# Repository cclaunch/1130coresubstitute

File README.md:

1130 Core Substitute

This project is intended for IBM 1130 systems where a core memory compartment is nonfunctional and unlikely to be restored to reliable operation. The printed circuit board is inserted at the top of the core compartment and is connected via the top cables T1, T3 and T4 that are normally plugged into the SLT board for the compartment. 

It is based around a Magnetoresistive Random Access Memory (MRAM) which provides the same non-volatility as core memory even after two decades sitting without power. MRAM has infinite read and write cycles, unlike flash memory, thus it is very suitable for use in a computer.

One would disconnect the four voltage rails to the core memory compartment (+6, +3, -3 and +12) so that the compartment itself is inert. The new PCB fits in the space at the top of the compartment where the top cables were connected. It requires only three wires to connect it to the +12V and ground rails of the 1130 system. 

This first version was developed for a particular 1130 system I restored, one with 8K of 3.6 microsecond core. This fits in the B gate in compartment C1. The SLT board has a core memory stack mounted in the center and SLT cards arrayed around the outside of the stack to provide the logic to make the core work. 

The same board can be enhanced to connect to cable T2, for machines with more than 8K of memory (or any 2.2 microsecond core memory model). Assuming the machine is configured for larger memory sizes so that the proper address lines are implemented in the device controllers and central processor, this single board could implement up to the maximum 32K word memory capacity. I will outline how the enhancement might be accomplished in a document in this repository.

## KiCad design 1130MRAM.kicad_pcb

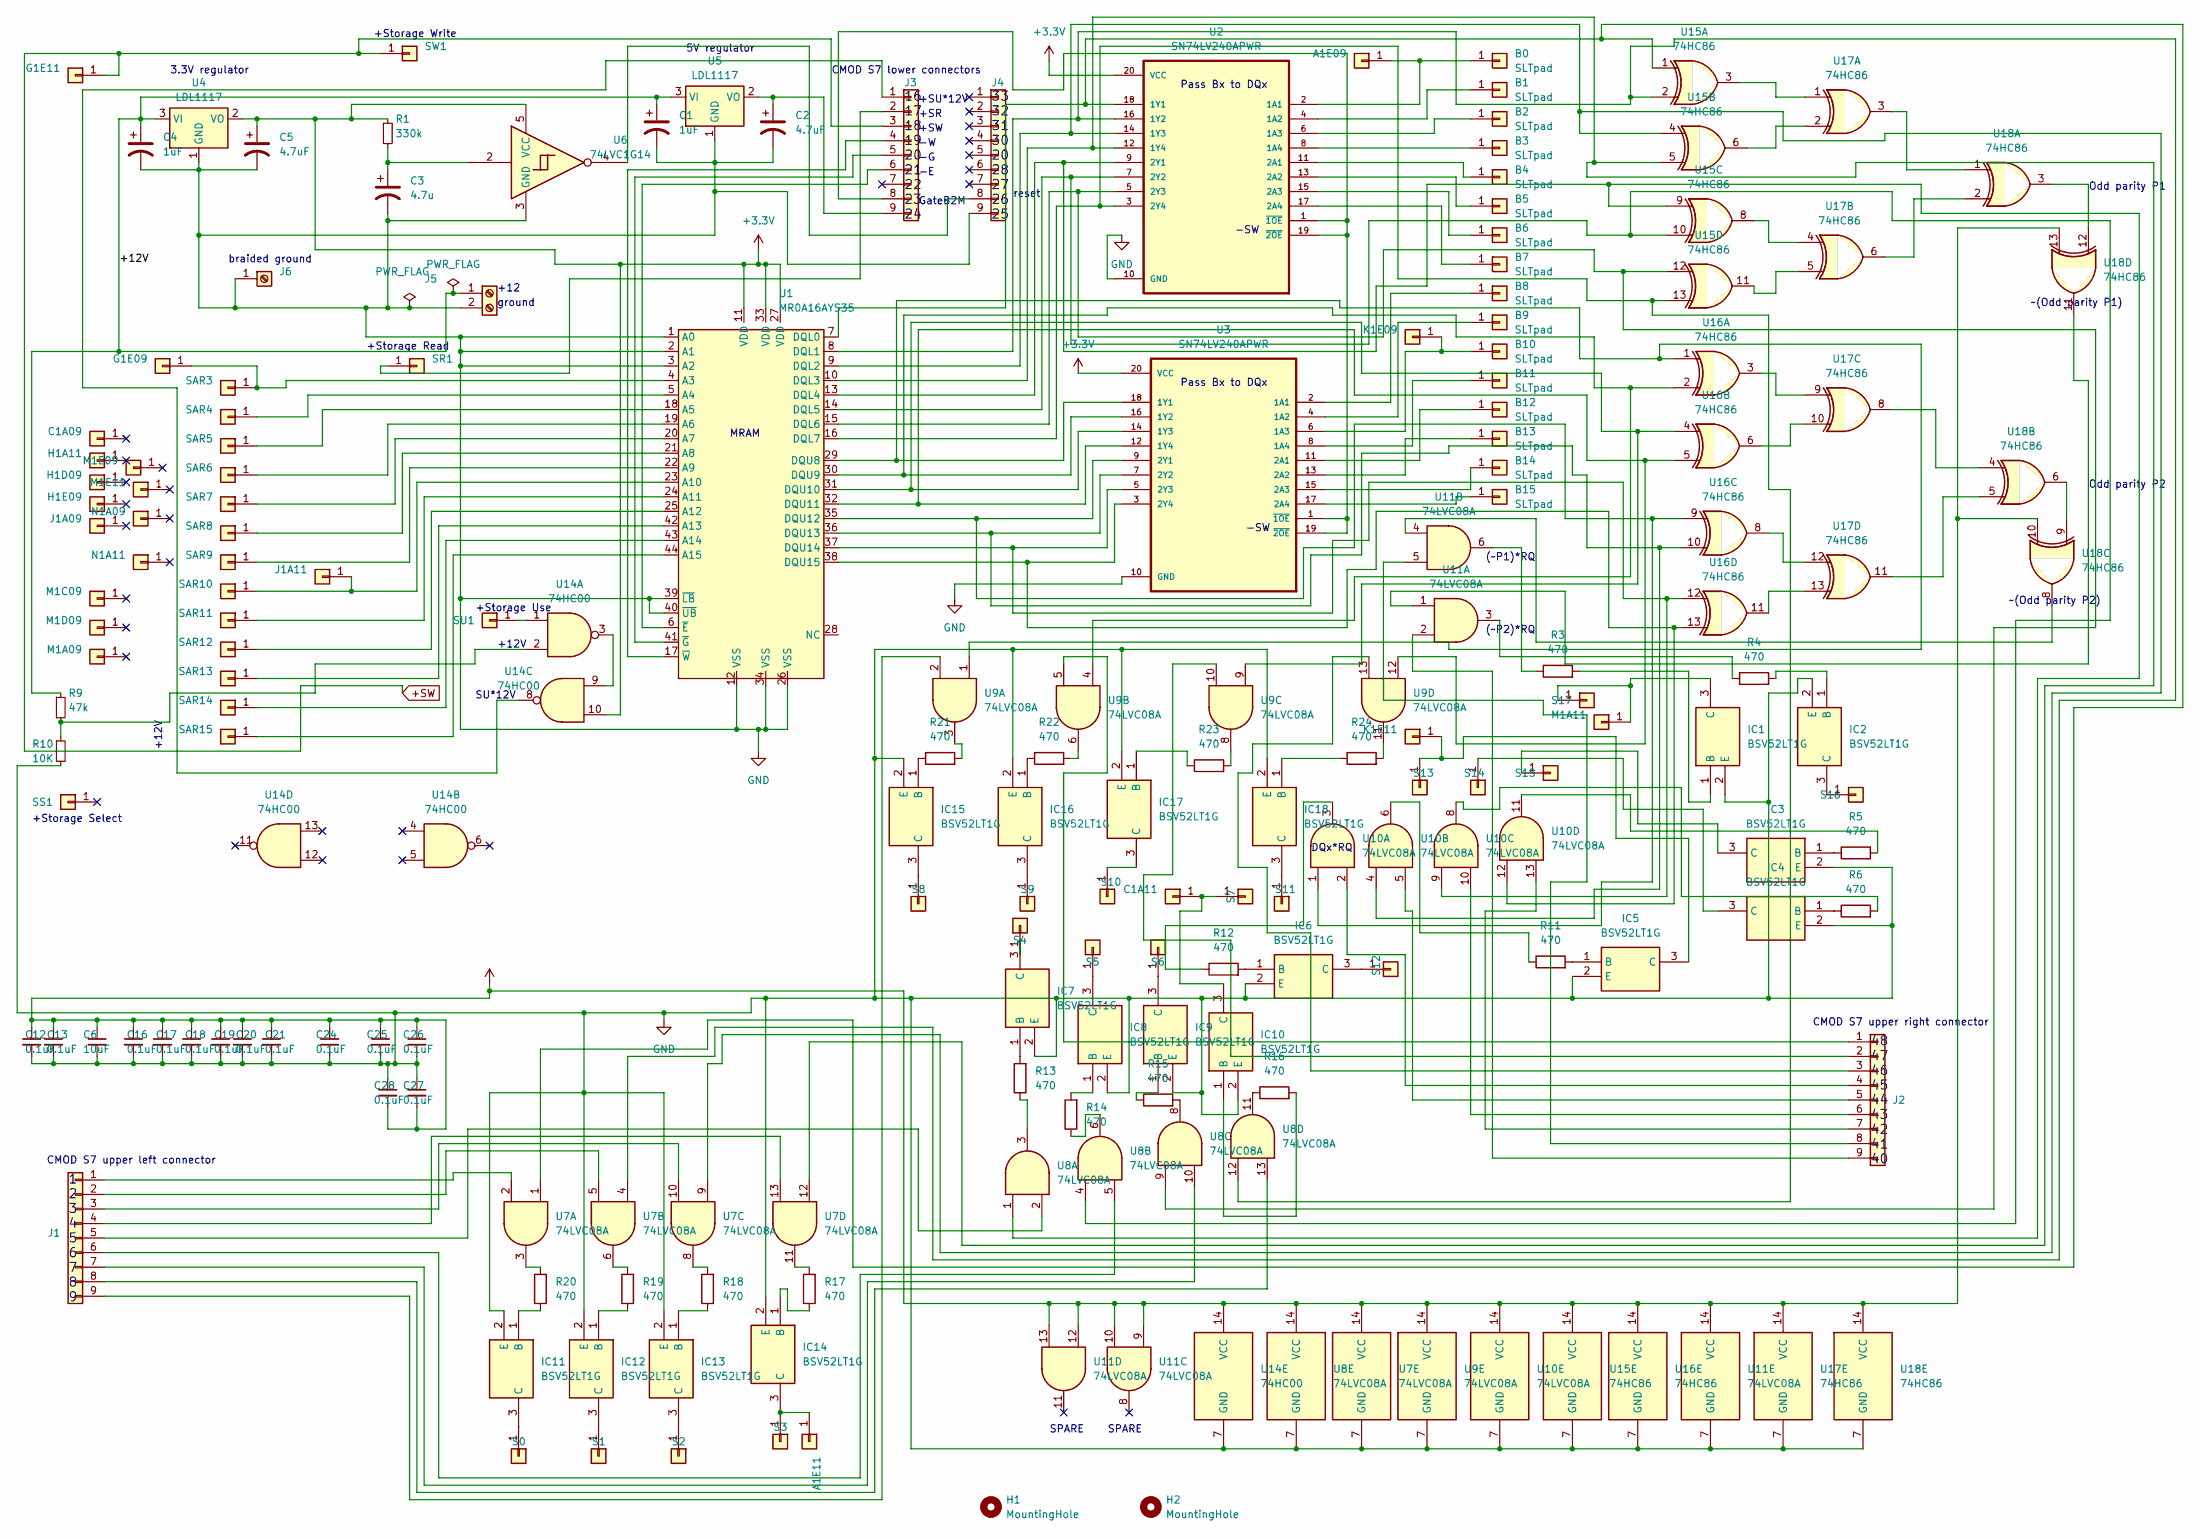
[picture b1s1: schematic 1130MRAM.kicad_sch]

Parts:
A1E09, A1E11: SLTpad; SLT
B0, B1, B2, B3, B4, B5, B6, B7, B8, B9, B10, B11, B12, B13, B14, B15: SLTpad; SLT
C1, C4: 1uF; C_0805_2012Metric
C1A09, C1A11: SLTpad; SLT
C2, C5: 4.7uF; C_0805_2012Metric
C3: 4.7u; C_0805_2012Metric
C6: 10uF; C_0805_2012Metric
C12, C13, C16, C17, C18, C19, C20, C21, C24, C25, C26, C27, C28: 0.1uF; C_0603_1608Metric
G1E09, G1E11: SLTpad; SLT
H1, H2: MountingHole; MountingHole_4.3mm_M4
H1A11, H1D09, H1E09: SLTpad; SLT
IC1, IC2, IC3, IC4, IC5, IC6, IC7, IC8, IC9, IC10, IC11, IC12, IC13, IC14, IC15, IC16, IC17, IC18: BSV52LT1G; SOT-23; Manufacturer_Part_Number BSV52LT1G; Mouser Part Number 863-BSV52LT1G
J1, J2, J3, J4: Conn_01x09_MountingPin; PinSocket_1x09_P2.54mm_Vertical
J1A09, J1A11: SLTpad; SLT
J5: Screw_Terminal_01x03; TerminalBlock_WAGO_236-102_1x02_P5.00mm_45Degree
J6: Screw_Terminal_01x01; TerminalBlock_WAGO_236-101_1x01_P5.00mm_45Degree
K1E09, K1E11: SLTpad; SLT
M1A09, M1A11, M1C09, M1D09, M1E09, M1E11: SLTpad; SLT
N1A09, N1A11: SLTpad; SLT
R1: 330k; R_0805_2012Metric
R3, R4, R5, R6, R11, R12, R13, R14, R15, R16, R17, R18, R19, R20, R21, R22, R23, R24: 470; R_0805_2012Metric
R9: 47k; R_0805_2012Metric
R10: 10K; R_0805_2012Metric
S0, S1, S2, S3, S4, S5, S6, S7, S8, S9, S10, S11, S12, S13, S14, S15, S16, S17: SLTpad; SLT
SAR3, SAR4, SAR5, SAR6, SAR7, SAR8, SAR9, SAR10, SAR11, SAR12, SAR13, SAR14, SAR15: SLTpad; SLT
SR1: SLTpad; SLT
SS1: SLTpad; SLT
SU1: SLTpad; SLT
SW1: SLTpad; SLT
U1: MR0A16AYS35; MR0A16A
U2, U3: SN74LV240APWR; sn74lvc244a
U4, U5: LDL1117; SOT-223-3_TabPin2
U6: 74LVC1G14; SOT-23-5_HandSoldering
U7, U8, U9, U10, U11: 74LVC08A; TSSOP-14_4.4x5mm_P0.65mm
U14: 74HC00; SOIC-14_3.9x8.7mm_P1.27mm
U15, U16, U17, U18: 74HC86; TSSOP-14_4.4x5mm_P0.65mm

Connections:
+3.3V: C5.1, C6.1, C12.1, C13.1, C16.1, C17.1, C18.1, C19.1, C20.1, C21.1, C24.1, C25.1, C26.1, C27.2, C28.2, R1.1, U1.11 (VDD), U1.27 (VDD), U1.33 (VDD), U2.20 (VCC), U3.20 (VCC), U4.2 (VO), U6.5 (VCC), U7.14 (VCC), U8.14 (VCC), U9.14 (VCC), U10.14 (VCC), U11.9, U11.10, U11.12, U11.13, U11.14 (VCC), U14.10, U14.14 (VCC), U15.14 (VCC), U16.14 (VCC), U17.14 (VCC), U18.10, U18.13, U18.14 (VCC)
+SW: G1E11.1, J3.3, SW1.1
/+12V: C1.1, C4.1, J5.1, R9.1, U4.3 (VI), U5.3 (VI)
GND: C1.2, C2.2, C3.2, C4.2, C5.2, C6.2, C12.2, C13.2, C16.2, C17.2, C18.2, C19.2, C20.2, C21.2, C24.2, C25.2, C26.2, C27.1, C28.1, IC1.2 (E), IC2.2 (E), IC3.2 (E), IC4.2 (E), IC5.2 (E), IC6.2 (E), IC7.2 (E), IC8.2 (E), IC9.2 (E), IC10.2 (E), IC11.2 (E), IC12.2 (E), IC13.2 (E), IC14.2 (E), IC15.2 (E), IC16.2 (E), IC17.2 (E), IC18.2 (E), J4.9, J5.2, J6.1, R10.2, U1.1 (A0), U1.2 (A1), U1.3 (A2), U1.12 (VSS), U1.26 (VSS), U1.34 (VSS), U1.39 (~LB), U1.40 (~UB), U2.10 (GND), U3.10 (GND), U4.1 (GND), U5.1 (GND), U6.3 (GND), U7.7 (GND), U8.7 (GND), U9.7 (GND), U10.7 (GND), U11.7 (GND), U14.7 (GND), U15.7 (GND), U16.7 (GND), U17.7 (GND), U18.7 (GND)
unnamed: A1E09.1, B0.1, U2.2 (1A1)
unnamed: A1E11.1, IC14.3 (C), S3.1
unnamed: B1.1, U2.4 (1A2)
unnamed: B2.1, U2.6 (1A3)
unnamed: B3.1, U2.8 (1A4)
unnamed: B4.1, U2.11 (2A1)
unnamed: B5.1, U2.13 (2A2)
unnamed: B6.1, U2.15 (2A3)
unnamed: B7.1, U2.17 (2A4)
unnamed: B8.1, U3.2 (1A1)
unnamed: B9.1, U3.4 (1A2)
unnamed: B10.1, K1E09.1, U3.6 (1A3)
unnamed: B11.1, U3.8 (1A4)
unnamed: B12.1, U3.11 (2A1)
unnamed: B13.1, U3.13 (2A2)
unnamed: B14.1, U3.15 (2A3)
unnamed: B15.1, U3.17 (2A4)
unnamed: C1A11.1, IC10.3 (C), S7.1
unnamed: C3.1, R1.2, U6.2
unnamed: G1E09.1, SAR3.1, U1.4 (A3)
unnamed: IC1.1 (B), R3.2
unnamed: IC1.3 (C), M1A11.1, S17.1
unnamed: IC2.1 (B), R4.2
unnamed: IC2.3 (C), S16.1
unnamed: IC3.1 (B), R5.1
unnamed: IC3.3 (C), S15.1
unnamed: IC4.1 (B), R6.1
unnamed: IC4.3 (C), S14.1
unnamed: IC5.1 (B), R11.2
unnamed: IC5.3 (C), K1E11.1, S13.1
unnamed: IC6.1 (B), R12.2
unnamed: IC6.3 (C), S12.1
unnamed: IC7.1 (B), R13.2
unnamed: IC7.3 (C), S4.1
unnamed: IC8.1 (B), R14.2
unnamed: IC8.3 (C), S5.1
unnamed: IC9.1 (B), R15.1
unnamed: IC9.3 (C), S6.1
unnamed: IC10.1 (B), R16.2
unnamed: IC11.1 (B), R20.1
unnamed: IC11.3 (C), S0.1
unnamed: IC12.1 (B), R19.1
unnamed: IC12.3 (C), S1.1
unnamed: IC13.1 (B), R18.1
unnamed: IC13.3 (C), S2.1
unnamed: IC14.1 (B), R17.1
unnamed: IC15.1 (B), R21.1
unnamed: IC15.3 (C), S8.1
unnamed: IC16.1 (B), R22.1
unnamed: IC16.3 (C), S9.1
unnamed: IC17.1 (B), R23.1
unnamed: IC17.3 (C), S10.1
unnamed: IC18.1 (B), R24.1
unnamed: IC18.3 (C), S11.1
unnamed: J1.1, U7.2
unnamed: J1.2, U7.5
unnamed: J1.3, U7.10
unnamed: J1.4, U7.13
unnamed: J1.5, U8.2
unnamed: J1.6, U8.5
unnamed: J1.7, U8.10
unnamed: J1.8, U8.13
unnamed: J1.9, U9.2
unnamed: J1A11.1, SAR10.1, U1.23 (A10)
unnamed: J2.1, U9.5
unnamed: J2.2, U9.10
unnamed: J2.3, U9.13
unnamed: J2.4, U10.2
unnamed: J2.5, U10.5
unnamed: J2.6, U10.10
unnamed: J2.7, U10.13
unnamed: J2.8, U11.5
unnamed: J2.9, U11.2
unnamed: J3.1, U14.8
unnamed: J3.2, SR1.1
unnamed: J3.4, U1.17 (~W)
unnamed: J3.5, U1.41 (~G)
unnamed: J3.6, U1.6 (~E)
unnamed: J3.8, U2.1 (~1OE), U2.19 (~2OE), U3.1 (~1OE), U3.19 (~2OE)
unnamed: C2.1, J3.9, U5.2 (VO)
unnamed: J4.8, U6.4
unnamed: R3.1, U11.6
unnamed: R4.1, U11.3
unnamed: R5.2, U10.11
unnamed: R6.2, U10.8
unnamed: R9.2, R10.1, U14.2
unnamed: R11.1, U10.6
unnamed: R12.1, U10.3
unnamed: R13.1, U8.3
unnamed: R14.1, U8.6
unnamed: R15.2, U8.8
unnamed: R16.1, U8.11
unnamed: R17.2, U7.11
unnamed: R18.2, U7.8
unnamed: R19.2, U7.6
unnamed: R20.2, U7.3
unnamed: R21.2, U9.3
unnamed: R22.2, U9.6
unnamed: R23.2, U9.8
unnamed: R24.2, U9.11
unnamed: SAR4.1, U1.5 (A4)
unnamed: SAR5.1, U1.18 (A5)
unnamed: SAR6.1, U1.19 (A6)
unnamed: SAR7.1, U1.20 (A7)
unnamed: SAR8.1, U1.21 (A8)
unnamed: SAR9.1, U1.22 (A9)
unnamed: SAR11.1, U1.24 (A11)
unnamed: SAR12.1, U1.25 (A12)
unnamed: SAR13.1, U1.42 (A13)
unnamed: SAR14.1, U1.43 (A14)
unnamed: SAR15.1, U1.44 (A15)
unnamed: SU1.1, U14.1
unnamed: U1.7 (DQL0), U2.18 (1Y1), U7.1, U15.1
unnamed: U1.8 (DQL1), U2.16 (1Y2), U7.4, U15.2
unnamed: U1.9 (DQL2), U2.14 (1Y3), U7.9, U15.4
unnamed: U1.10 (DQL3), U2.12 (1Y4), U7.12, U15.5
unnamed: U1.13 (DQL4), U2.9 (2Y1), U8.1, U15.9
unnamed: U1.14 (DQL5), U2.7 (2Y2), U8.4, U15.10
unnamed: U1.15 (DQL6), U2.5 (2Y3), U8.9, U15.12
unnamed: U1.16 (DQL7), U2.3 (2Y4), U8.12, U15.13
unnamed: U1.29 (DQU8), U3.18 (1Y1), U9.1, U16.1
unnamed: U1.30 (DQU9), U3.16 (1Y2), U9.4, U16.2
unnamed: U1.31 (DQU10), U3.14 (1Y3), U9.9, U16.4
unnamed: U1.32 (DQU11), U3.12 (1Y4), U9.12, U16.5
unnamed: U1.35 (DQU12), U3.9 (2Y1), U10.1, U16.9
unnamed: U1.36 (DQU13), U3.7 (2Y2), U10.4, U16.10
unnamed: U1.37 (DQU14), U3.5 (2Y3), U10.9, U16.12
unnamed: U1.38 (DQU15), U3.3 (2Y4), U10.12, U16.13
unnamed: U11.1, U18.11
unnamed: U11.4, U18.8
unnamed: U14.3, U14.9
unnamed: U15.3, U17.1
unnamed: U15.6, U17.2
unnamed: U15.8, U17.4
unnamed: U15.11, U17.5
unnamed: U16.3, U17.9
unnamed: U16.6, U17.10
unnamed: U16.8, U17.12
unnamed: U16.11, U17.13
unnamed: U17.3, U18.1
unnamed: U17.6, U18.2
unnamed: U17.8, U18.4
unnamed: U17.11, U18.5
unnamed: U18.6, U18.9
unnamed: U18.3, U18.12

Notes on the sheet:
+12V
+SW
3.3V regulator
+Storage Read
Pass Bx to DQx
CMOD S7 upper right connector
1 2 3 4 5 6 7 8 9
-SW
+Storage Write
Odd parity P2
(~P2)*RQ
GateB2M
SPARE
braided ground
CMOD S7 upper left connector
33 32 31 30 20 28 27 26 25
+12
reset
MRAM
+SR
(~P1)*RQ
ground
~(Odd parity P1)
48 47 46 45 44 43 42 41 40
DQx*RQ
+Storage Select
SU*12V
+Storage Use
+SU*12V
16 17 18 19 20 21 22 23 24
5V regulator
Odd parity P1
~(Odd parity P2)
CMOD S7 lower connectors

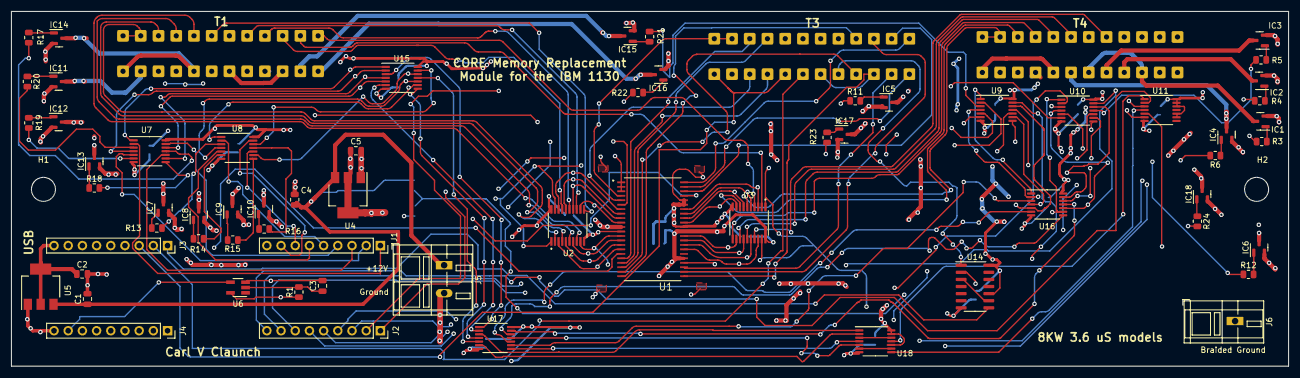
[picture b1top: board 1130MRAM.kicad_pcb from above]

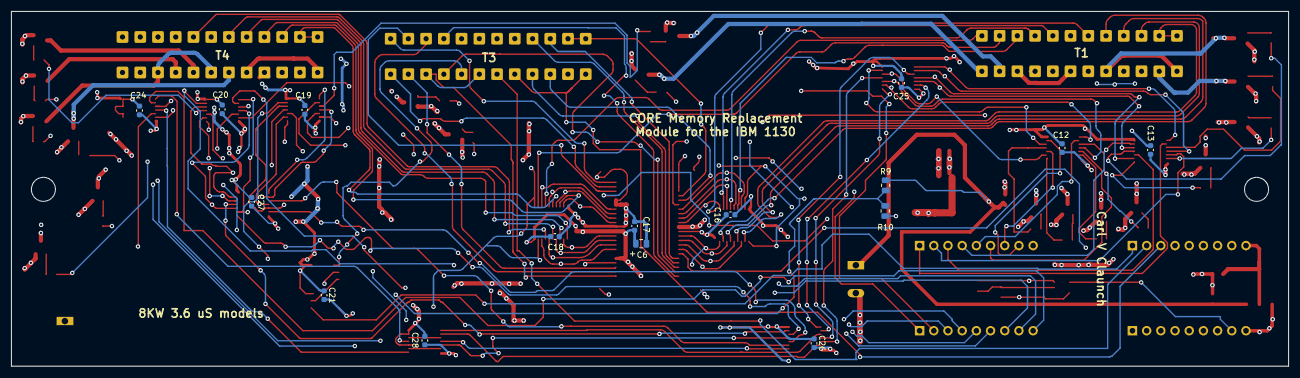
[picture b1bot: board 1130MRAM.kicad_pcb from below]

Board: 4 copper layers, 228.6 x 63.5 mm, 154 parts (88 on the bottom side), 149 nets.

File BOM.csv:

Index,DigiKey Part #,Manufacturer Part Number,Manufacturer,Description,Quantity,Unit Price,Extended Price
1,819-1007-ND,MR0A16AYS35,Everspin Technologies Inc.,IC RAM 1MBIT PARALLEL 44TSOP2,1,$16.12 ,$16.12 
2,296-12358-1-ND,SN74LV240APWR,Texas Instruments,IC BUFFER INVERT 5.5V 20-TSSOP,2,$0.85 ,$1.70 
3,1727-5965-1-ND,74HC86PW,Nexperia USA Inc.,IC GATE XOR 4CH 2-INP 14TSSOP,4,$0.23 ,$0.92 
4,296-1221-1-ND,SN74LVC08APWR,Texas Instruments,IC GATE AND 4CH 2-INP 14TSSOP,5,$0.40 ,$2.00 
5,296-1187-1-ND?,SN74HC00DR?,Texas Instruments,IC GATE NAND 4CH 2-INP 14SOIC,1,$0.23 ,$0.23 
6,A100889CT-ND ,5-87623-4,TE Connectivity,SLT connector pins,72,$0.65 ,$46.64 
7,399-C0603C104K3RACTUCT-ND,C0603C104K3RACTU,Kemet,CAP CER 0.1UF 25V X7R 0603,17,$0.03 ,$0.44 
8,497-17239-1-ND,LDL1117S33R,STM Microelectronics,IC REG LINEAR 3.3V 1.2A SOT-223,1,$0.36 ,$0.36 
9,1276-1066-1-ND,CL21B105KAFNNNE,Samsung,CAP CER 1UF 25V X7R 0805,2,$0.08 ,$0.16 
10,587-2990-1-ND,TMK212AB7475KG,Tayo Yuden,CAP CER 4.7UF 25V X7R 0805,3,$0.23 ,$0.69 
11,BSV52LT1G,BSV52LT1G,OnSemi,TRANS NPN 12V 0.1A SOT23-3,18,$0.29 ,$5.22 
12,ERA-6AEB202V,ERA-6AEB202V,Panasonic,RES SMD 2K OHM 0.1% 1/8W 0805,18,$0.06 ,$1.10 
13,497-6447-2-ND,LD1117S50TR,STM Microelectronics,IC REG LINEAR 5V 1.2A SOT-223,1,$0.39 ,$0.39 
14,RMCF0805FT330KCT-ND,RMCF0805FT330K,Stackpole Electronics Inc,RES 330K OHM 1% 1/8W 0805,1,$0.39 ,$0.39 
15,296-11607-1-ND,SN74LVC1G14DBVR,Texas Instruments,IC INVERTER 1CH 1-INP SOT23-5,1,$0.12 ,$0.12 
16,1286-1205-ND,410-376,DIgilent,CMOD S7: BREADBOARDABLE SPARTAN7,1,$99.00 ,$99.00 
17,2946-236-101-ND,236-101,Wago,STACKABLE PCB TERMINAL BLOCK; 2.,1,$1.22 ,$1.22 
18,2946-236-102-ND,236-102,Wago,PCB TERMINAL BLOCK; 2.5 MM; PIN,1,$2.49 ,$2.49 
19,,,,,1,$0.00 ,$0.00 
,,,,Fedex Digikey shipment charge,1,$6.99 ,$6.99 
,,,,tax,,,$12.54 
,,,,PCB + shipping charge,1,90,$90.00 
,,,,Stencil for solder paste,,,$0.00 
,,,,,,subtotal,$288.73

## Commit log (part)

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2025-07-27 Initial creation of repository
2025-07-27 Initial design KiCAD files
2025-07-28 Completed design V1
    prior to verification
2025-07-28 New document
    Describes the logic and operation of the board.
2025-07-28 Create LICENSE
2025-07-29 Latest version with fixes
    fixed parity circuits, went to 4 layer board
2025-07-30 Annotations and cleanup
2025-07-30 Corrections to design
2025-07-30 Updated documentation
2025-07-30 Updated Bill of Materials
    Includes Digikey product numbers, prices and quantities.
    Almost complete
2025-08-13 Debugged version of KiCAD files
    Created project library for the symbols and footprints used with this design
2025-08-13 Cleaned up after bench testing
    also put symbols and footprints into project libraries
2025-08-13 Updated theory of operations document
    Reflecting results of bench testing
2025-08-13 early draft of document
    early draft of installation and testing instructions
2025-09-14 Modifications after testing
2025-09-16 Enhancement after testing
2025-09-16 Reflect changes after testing
2025-09-18 Backfeed protection circuit added
    Blocks backfeed of voltage from 1130 inputs to the PCB unless the +12V power rail is active
2025-09-18 Now with onboard regulator for 3.3V
2025-09-18 Onboard voltage regulator change
2025-09-18 cosmetic tweak
2025-09-27 Post debugging version
    tie together pins that have duplicate signals on connectors T1, T3 and T4, as was done on the SLT backplane we are replacing. Gets the control, address, data and sense signals correctly routed from 1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
2025-09-27 Post debugging version
    Handles duplicate pins on cables T1, T3 and T4 that are only bridged on the IBM SLT backplane we are replacing with this board. Gets control, address, data and sense signals to the circuitry on the P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
2025-09-27 post debugging version
    handles duplicate pins on T1, T3 and T4 correctly.
2025-10-03 Switched to 74LCX38 for better output drive
    prior chip had insufficient current sink to set the 1130 flip flop
2025-10-03 Switch to 74LCX38 for better output drive
    prior open drain gate had insufficent current sink capacity to set the 1130's B register flipflop
2025-10-03 Updated Bill of Materials
    new power, new low side ground lift circuit, change to 74LCX38 chips, plus tariff increase on PCBs
2025-10-10 Tweaks
    Changed to make soldering of filter capacitors easier next to certain chips
2025-10-10 Edits for readability
2025-10-13 Corrected defect in design
    Prior design optimization led to a failure mode that is experienced on the IBM 1130. Corrected the issue.
2025-11-12 Newest version of the PCB
    based on testing with the 1130, the PCB was modified substantially
2025-11-12 Newest version of PCB design documented
2025-11-12 Corresponding to newest version of PCB
2025-12-22 Changes after testing
    tweaks to design, components, and documentation.
2026-03-19 New version leveraging FPGA
    Changed board to be driven by an FPGA
2026-03-19 files associated with new design of board
2026-03-19 files associated with new board design
